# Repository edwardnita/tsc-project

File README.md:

# OpenBook - eBook Reader

**Autor:** Nita Eduard-Eugen
**Data:** 06 Aprilie 2025, updated pe 14 Aprilie 2025

## Bill of Materials (BOM)

| Component                | Link                                                                                                                      | Datasheet                                                                                                              |
|:-------------------------|:--------------------------------------------------------------------------------------------------------------------------|:-----------------------------------------------------------------------------------------------------------------------|
| BME680                   | [Link](https://www.snapeda.com/parts/BME680/Bosch/view-part/?welcome=home)                                                | [Datasheet](https://www.bosch-sensortec.com/media/boschsensortec/downloads/datasheets/bst-bme680-ds001.pdf)            |
| BUTTON                   | [Link](https://industry.panasonic.com/global/en/products/control/switch/light-touch/number/evqpuj02k)                     | [Datasheet](https://www.lcsc.com/datasheet/lcsc_datasheet_2201121800_PANASONIC-EVQPUJ02K_C2936858.pdf)                 |
| R0402                    | [Link](https://componentsearchengine.com/part-view/R0402%201%25%20100%20K%20(RC0402FR-07100KL)/YAGEO)                     | [Datasheet](https://www.resistor.com/assets/pdf/0402tstd.pdf)                                                          |
| CPH3225A                 | [Link](https://www.snapeda.com/parts/CPH3225A/Seiko+Instruments/view-part/?ref=eda)                                       | [Datasheet](https://octopart.com/datasheet/cph3225a-seiko-25340571)                                                    |
| EVQPUJ02K                | [Link](https://industry.panasonic.com/global/en/products/control/switch/light-touch/number/evqpuj02k)                     | [Datasheet](https://www.lcsc.com/datasheet/lcsc_datasheet_2201121800_PANASONIC-EVQPUJ02K_C2936858.pdf)                 |
| KP-1608SURCK             | [Link](https://www.snapeda.com/parts/KP-1608SURCK/Kingbright/view-part/?ref=search&t=LED%200603)                          | [Datasheet](https://media.elv.com/file/107153_led_surck1608_data.pdf)                                                  |
| USBLC6-2SC6Y             | [Link](https://www.snapeda.com/parts/USBLC6-2SC6Y/STMicroelectronics/view-part/?ref=eda)                                  | [Datasheet](https://www.digikey.com/en/htmldatasheets/production/1375342/0/0/1/usblc6-2sc6y)                           |
| SD0805S020S1R0           | [Link](https://ro.mouser.com/ProductDetail/KYOCERA-AVX/SD0805S020S1R0?qs=jCA%252BPfw4LHbpkAoSnwrdjw%3D%3D)                | [Datasheet](https://www.alldatasheet.com/view.jsp?Searchword=SD0805S&sField=2)                                         |
| PGB1010603MR             | [Link](https://www.snapeda.com/parts/PGB1010603MR/Littelfuse/view-part/?ref=eda)                                          | [Datasheet](https://www.alldatasheet.com/view.jsp?Searchword=Pgb1010603mr)                                             |
| BD5229G-TR               | [Link](https://componentsearchengine.com/part-view/BD5229G-TR/ROHM%20Semiconductor)                                       | [Datasheet](https://www.lcsc.com/datasheet/lcsc_datasheet_2201131330_ROHM-Semicon-BD5229G-TR_C962636.pdf)              |
| XC6220A331MR-G           | [Link](https://componentsearchengine.com/part-view/XC6220A331MR-G/Torex)                                                  | [Datasheet](https://www.alldatasheet.com/view.jsp?Searchword=Xc6220)                                                   |
| USB4110-GF-A             | [Link](https://componentsearchengine.com/part-view/USB4110-GF-A/GCT%20(GLOBAL%20CONNECTOR%20TECHNOLOGY))                  | [Datasheet](https://gct.co/files/drawings/usb4110.pdf)                                                                 |
| Adafruit LEDCHIP-LED0603 | [Link](https://eu.mouser.com/ProductDetail/Adafruit/4208?qs=PzGy0jfpSMtbScLbr0L5dw%3D%3D)                                 | [Datasheet](https://www.arrow.com/en/manufacturers/adafruit-industries/datasheets)                                     |
| Bobina                   | [Link](https://store.comet.srl.ro/Catalogue/Product/43497/)                                                               | [Datasheet](https://www.scribd.com/document/814581278/Datasheet-Bobina)                                                |
| PFMF                     | [Link](https://www.mouser.co.uk/ProductDetail/EPCOS-TDK/B72520T0350K062?qs=dEfas%2FXlABIszF52uu7vrg%3D%3D)                | [Datasheet](https://ro.mouser.com/c/ds/circuit-protection/thermistors/resettable-fuses-pptc/?m=Schurter&series=PFMF)   |
| DMG2305UX-7              | [Link](https://componentsearchengine.com/part-view/DMG2305UX-7/Diodes%20Incorporated)                                     | [Datasheet](https://www.mouser.com/datasheet/2/115/DMG2305UX-266242.pdf)                                               |
| Si1308EDL-T1-GE3         | [Link](https://componentsearchengine.com/part-view/SI1308EDL-T1-GE3/Vishay)                                               | [Datasheet](https://www.alldatasheet.com/view.jsp?Searchword=Si1308edl)                                                |
| MCP73831T-5ACI/OT        | [Link](https://www.mouser.co.uk/ProductDetail/Microchip-Technology/MCP73831T-5ACI-OT?qs=hH%252BOa0VZEiAcgAcEkuamXg%3D%3D) | [Datasheet](https://ww1.microchip.com/downloads/en/DeviceDoc/MCP73831-Family-Data-Sheet-DS20001984H.pdf)               |
| SMD Solder               | [Link](https://grabcad.com/library/solder-jumpers-1)                                                                      |                                                                                                                        |
| W25Q512JVEIQ             | [Link](https://www.snapeda.com/parts/ESP32-C6-WROOM-1-N8/Espressif+Systems/view-part/?ref=eda)                            | [Datasheet](https://www.mouser.com/datasheet/2/949/W25Q512JV_SPI_RevB_06252019_KMS-2487502.pdf)                        |
| ESP32-C6-WROOM-1-N8      | [Link](https://www.snapeda.com/parts/ESP32-C6-WROOM-1-N8/Espressif+Systems/view-part/?ref=eda)                            | [Datasheet](https://www.mouser.com/catalog/specsheets/Espressif_ESP32_C6_WROOM_1%20_Datasheet_V0.1_PRELIMINARY_en.pdf) |
| DS3231SN#                | [Link](https://www.snapeda.com/parts/DS3231SN%23/Analog+Devices/view-part/?ref=eda)                                       | [Datasheet](https://www.alldatasheet.com/view.jsp?Searchword=Ds3231sn%20datasheet)                                     |
| MAX17048G+T10            | [Link](https://www.snapeda.com/parts/MAX17048G+T10/Analog+Devices/view-part/?ref=eda)                                     | [Datasheet](https://www.alldatasheet.com/view.jsp?Searchword=Max17048)                                                 |

## Descriere Hardware

OpenBook este un e-reader open source care folosește ESP32-C6 ca unitate de control. Dispozitivul se concentrează pe eficiență energetică, conectivitate și afișaj de calitate tip e-ink.

### Microcontroller: ESP32-C6

- Procesor: RISC-V 32-bit @ 160 MHz
- Interfețe utilizate:
  - **SPI**: pentru e-paper
  - **I2C**: pentru BME688 și MAX17048
  - **USB-C**: pentru alimentare și transfer date
  - **GPIO**: pentru butoane și control încărcare

### Display: E-paper 7.5”

- Rezoluție: 800x480 px, alb-negru
- Interfață: SPI
- Refresh complet < 1s, parțial < 0.5s
- Folosit pentru afișare cărți, meniuri, informații senzori

### Senzor Mediu: BME688

- Măsoară: temperatură, umiditate, presiune, calitate aer (eCO2, TVOC)
- I2C, 400kHz
- Datele sunt afișate în interfața de utilizator și pot fi logate

### Power Management:

- **Baterie**: 2500mAh Li-Po 3.7V
- **MAX17048**: estimează nivelul de încărcare
- **MCP73831**: controlează încărcarea prin USB-C (1A max)
- **Consum**:
  - Active: ~120mA
  - Sleep: <50µA

### Butoane:

- 3 butoane fizice pentru meniu, navigare și selectare
- Interfață GPIO, debounce hardware/firmware

### USB-C:

- Alimentare și transfer fișiere (USB MSC)
- Protecție ESD

### PCB și Carcasă:

- PCB 2-layer cu layout optimizat termic și EMC
- ENIG finish
- Carcasă ABS/PC, 250g, ergonomică, rezistentă la praf și stropire (IP estimat: IP52)

## Pini ESP32-C6

| Componentă       | Pin ESP32-C6 | Motiv Alegere           |
| ---------------- | ------------ | ----------------------- |
| E-Paper SPI CLK  | GPIO10       | SPI hardware            |
| E-Paper SPI MOSI | GPIO11       | SPI hardware            |
| E-Paper CS       | GPIO9        | Chip Select dedicat     |
| BME688 I2C SDA   | GPIO4        | I2C standard            |
| BME688 I2C SCL   | GPIO5        | I2C standard            |
| MAX17048 SDA     | GPIO4        | I2C partajat cu BME688  |
| MAX17048 SCL     | GPIO5        | I2C partajat cu BME688  |
| Buton 1          | GPIO6        | Navigare                |
| Buton 2          | GPIO7        | Selectare               |
| Buton 3          | GPIO8        | Back/Menu               |
| USB D+           | GPIO18       | USB funcționalitate MSC |
| USB D-           | GPIO19       | USB funcționalitate MSC |

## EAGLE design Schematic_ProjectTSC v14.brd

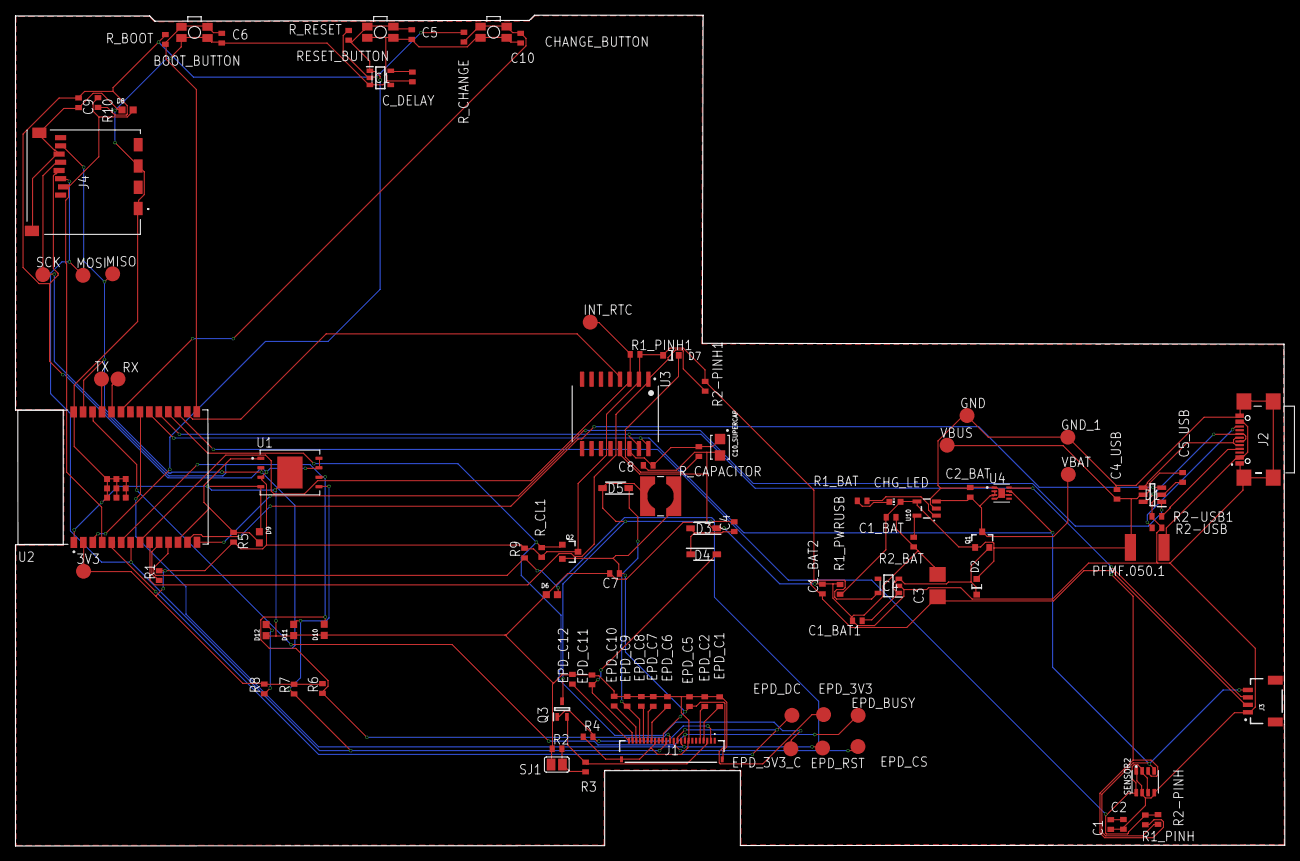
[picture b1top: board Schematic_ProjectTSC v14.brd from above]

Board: 2 copper layers, 170.2 x 111.4 mm, 103 parts (0 on the bottom side), 56 nets.

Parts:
3V3: TPTP20R; TP20R
BOOT_BUTTON: BUTTON_CUSYOMV1; MYBUTTON
C1: 100uF; EAGLE-LTSPICE_C0402
C1_BAT, C2_BAT: 4.7uF; ESP32_WROVER_EAGLE-LTSPICE_C0402
C1_BAT1, C1_BAT2, C5_USB: 4.7uF; EAGLE-LTSPICE_C0402
C2, C4_USB, C8, C9: 100nF; EAGLE-LTSPICE_C0402
C3: 100uF TANT; RCL_CT3528
C4: 4.7uF/25V; ESP32_WROVER_EAGLE-LTSPICE_C0402
C5: 1uF; ESP32_WROVER_EAGLE-LTSPICE_C0402
C6, C10: 100nF; ESP32_WROVER_EAGLE-LTSPICE_C0402
C7: 10uF; ESP32_WROVER_EAGLE-LTSPICE_C0402
C10_SUPERCAP: CPH3225A; CAPCP3225X100N
CHANGE_BUTTON: BUTTON_CUSYOMV1; MYBUTTON
CHG_LED: ADAFRUIT_CHIP-LED0603
C_DELAY: 100nF; ESP32_WROVER_EAGLE-LTSPICE_C0402
D1: USBLC6-2SC6Y; SOT95P280X145-6N
D2, D7: ESP32_WROVER_AVX---SD0805S020S1R0_AVX_SD0805S020S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; ESP32_WROVER_AVX---SD0805S020S1R0_AVX_SD0805S020S1R0_0
D3, D4, D5: MBR0530; SOD3716X135N
D6, D8, D9, D10, D11, D12: PGB1010603MR; DIOC1608X36N
EPD_3V3, EPD_3V3_C: TPTP20R; TP20R
EPD_BUSY: TPTP20R; TP20R
EPD_C1, EPD_C2, EPD_C6, EPD_C7, EPD_C8, EPD_C9, EPD_C10, EPD_C11, EPD_C12: 1uF/50V; ESP32_WROVER_EAGLE-LTSPICE_C0402
EPD_C5: 0.1uF/50V; ESP32_WROVER_EAGLE-LTSPICE_C0402
EPD_CS: TPTP20R; TP20R
EPD_DC: TPTP20R; TP20R
EPD_RST: TPTP20R; TP20R
GND: TPTP20R; TP20R
GND_1: TPTP20R; TP20R
IC1: BD5229G-TR; SOT95P280X125-5N
IC4: XC6220A331MR-G; SOT95P280X120-5N
INT_RTC: TPTP20R; TP20R
J1: FH34SRJ-24S-0.5SH_99_; FH34SRJ24S05SH99
J2: SAMACSYS_PARTS_USB4110-GF-A; SAMACSYS_PARTS_USB4110GFA
J3: QWIIC_RIGHT_ANGLE; JST04_1MM_RA
J4: 112A-TAAR-R03_ATTEND; 112ATAARR03ATTEND
L1: 744043680IND_4828-WE-TPC_WRE; IND_4828-WE-TPC_WRE
MISO: TPTP20R; TP20R
MOSI: TPTP20R; TP20R
PFMF.050.1: ESP32C6_VARISTORCN1812; ESP32C6_VARISTOR_CT/CN1812
Q1, Q2: 20V/4.2A/52mΩ/1.4W; ESP32_WROVER_SPARKFUN-DISCRETESEMI_SOT23-3
Q3: SI1308EDL-T1-GE3; SOT65P210X110-3N
R1, R1_PINH, R1_PINH1, R2-PINH, R2-PINH1, R4, R5, R6, R7, R8, R9, R10: 10K; ESP32_WROVER_EAGLE-LTSPICE_R0402
R1_BAT: 200; ESP32_WROVER_EAGLE-LTSPICE_R0402
R1_PWRUSB: 100k; ESP32_WROVER_EAGLE-LTSPICE_R0402
R2: 2.2; ESP32_WROVER_EAGLE-LTSPICE_R0402
R2-USB: 5K1; ESP32_WROVER_EAGLE-LTSPICE_R0402
R2-USB1: 5k1; ESP32_WROVER_EAGLE-LTSPICE_R0402
R2_BAT: 2K; ESP32_WROVER_EAGLE-LTSPICE_R0402
R3: 0.47; ESP32_WROVER_EAGLE-LTSPICE_R0402
RESET_BUTTON: BUTTON_CUSYOMV1; MYBUTTON
RX: TPTP20R; TP20R
R_BOOT: 10K; ESP32_WROVER_EAGLE-LTSPICE_R0402
R_CAPACITOR: 15; ESP32_WROVER_EAGLE-LTSPICE_R0402
R_CHANGE: 10K; ESP32_WROVER_EAGLE-LTSPICE_R0402
R_CL1: 10K; ESP32_WROVER_EAGLE-LTSPICE_R0402
R_RESET: 10K; ESP32_WROVER_EAGLE-LTSPICE_R0402
SCK: TPTP20R; TP20R
SENSOR2: ESP32_WROVER_BME680_BME680; ESP32_WROVER_BME680_PSON80P300X300X100-8N
SJ1: SJ
TX: TPTP20R; TP20R
U1: W25Q512JVEIQ; SON127P600X800X80-9N
U2: ESP32-C6-WROOM-1-N8; XCVR_ESP32-C6-WROOM-1-N8
U3: DS3231SN#; SOIC127P1032X265-16N
U4: MAX17048G+T10; SON50P200X200X80-9N
U10: ESP32_WROVER_SPARKFUN-IC-POWER_MCP73831; ESP32_WROVER_SPARKFUN-IC-POWER_SOT23-5
VBAT: TPTP20R; TP20R
VBUS: TPTP20R; TP20R

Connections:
3V3: 3V3.TP, C1_BAT2.1, C3.+, C9.1, D7.2, IC1.2, IC4.5, J3.2, J4.P4, Q2.3, R1.2, R1_PINH1.2, R2-PINH1.2, R5.2, R6.2, R7.2, R8.2, R9.2, R10.2, R_BOOT.2, R_CHANGE.2, R_CL1.2, R_RESET.2, U1.3, U1.7, U1.8, U2.2, U3.2
32KHZ: R2-PINH1.1, U2.9, U3.1
DN: D1.4, J2.A7, J2.B7
DP: D1.6, J2.A6, J2.B6
EPD_3V3: C7.1, EPD_3V3.TP, EPD_C5.1, J1.15, J1.16, L1.2, Q2.2
EPD_3V3_C: EPD_3V3_C.TP, Q2.1, R_CL1.1, U2.18
EPD_BUSY: EPD_BUSY.TP, J1.9, U2.26
EPD_CS: D6.2, EPD_CS.TP, J1.12, R9.1, U2.11
EPD_DC: EPD_DC.TP, J1.11, U2.5
EPD_RST: EPD_RST.TP, J1.10, U2.21
FLASH_CS: D9.2, R5.1, U1.1, U2.12
GDR: J1.2, Q3.1, R4.2
GND: BOOT_BUTTON.1, BOOT_BUTTON.2, C1.2, C1_BAT.2, C1_BAT1.2, C1_BAT2.2, C2.2, C2_BAT.2, C3.-, C4_USB.2, C5.2, C5_USB.2, C6.2, C7.2, C8.2, C9.2, C10.2, C10_SUPERCAP.2, CHANGE_BUTTON.1, CHANGE_BUTTON.2, C_DELAY.2, D1.2, D3.1, D6.1, D8.1, D9.1, D10.1, D11.1, D12.1, EPD_C1.2, EPD_C2.2, EPD_C5.2, EPD_C6.2, EPD_C7.2, EPD_C8.2, EPD_C9.2, EPD_C10.2, EPD_C11.2, EPD_C12.2, GND.TP, GND_1.TP, IC1.3, IC4.2, J1.8, J1.17, J1.MP1, J1.MP2, J2.A1, J2.A12, J2.B1, J2.B12, J2.MP1, J2.MP2, J2.MP3, J2.MP4, J3.1, J4.G1, J4.G2, J4.G3, J4.G4, J4.P6, R1_PWRUSB.1, R2.1, R2-USB.2, R2-USB1.1, R2_BAT.1, R4.1, RESET_BUTTON.1, RESET_BUTTON.2, SENSOR2.1, SENSOR2.5, SENSOR2.7, SJ1.1, U1.4, U1.9, U2.1, U2.28, U2.29_1, U2.29_2, U2.29_3, U2.29_4, U2.29_5, U2.29_6, U2.29_7, U2.29_8, U2.29_9, U3.13, U4.1, U4.4, U4.6, U4.9, U10.2
GPIO8: R1.1, U2.10
I2C_PW: R1_PINH.2, R2-PINH.2, SENSOR2.2, SENSOR2.6, SENSOR2.8, U2.17
INT_RTC: INT_RTC.TP, R1_PINH1.1, U2.8, U3.3
IO/BOOT: BOOT_BUTTON.3, BOOT_BUTTON.4, C6.1, R_BOOT.1, U2.15
IO/CHANGE: C10.1, CHANGE_BUTTON.3, CHANGE_BUTTON.4, R_CHANGE.1, U2.23
MISO: D12.2, J4.P7, MISO.TP, R8.1, U1.2, U2.27
MOSI: D11.2, J1.14, J4.P3, MOSI.TP, R7.1, U1.5, U2.7
unnamed: C1_BAT1.1, D2.1, IC4.1, IC4.3, Q1.2
unnamed: J2.B5, R2-USB.1
unnamed: R2_BAT.2, U10.5
unnamed: J2.A5, R2-USB1.2
unnamed: C1.1, C2.1
unnamed: C4.1, D3.2, D4.1
unnamed: C_DELAY.1, IC1.5
unnamed: CHG_LED.C, R1_BAT.1
unnamed: R1_BAT.2, U10.1
unnamed: EPD_C2.1, J1.5
unnamed: EPD_C1.1, J1.4
unnamed: EPD_C12.1, J1.24
unnamed: D7.1, R_CAPACITOR.1
unnamed: EPD_C10.1, J1.22
unnamed: EPD_C8.1, J1.20
unnamed: EPD_C7.1, J1.19
unnamed: EPD_C6.1, J1.18
PREVGH: D5.1, EPD_C9.1, J1.21
PREVGL: D4.2, EPD_C11.1, J1.23
RESE: J1.3, Q3.2, R3.2
RESE': R2.2, R3.1, SJ1.2
RESET: C5.1, IC1.1, RESET_BUTTON.3, RESET_BUTTON.4, R_RESET.1, U2.3
RTC_RST: U2.16, U3.4
RX: RX.TP, U2.24
SCK: D10.2, J1.13, J4.P5, R6.1, SCK.TP, U1.6, U2.6
SCL: J3.4, R2-PINH.1, SENSOR2.4, U2.20, U3.16, U4.7
SDA: J3.3, R1_PINH.1, SENSOR2.3, U2.19, U3.15, U4.8
SRC: C4.2, D5.2, L1.1, Q3.3
SS_SD: D8.2, J4.P2, R10.1, U2.4
TX: TX.TP, U2.25
USB_D+: D1.1, U2.14
USB_D-: D1.3, U2.13
VBAT: C2_BAT.1, Q1.3, U4.2, U4.3, U10.3, VBAT.TP
VBUS: C1_BAT.1, C4_USB.1, C5_USB.1, CHG_LED.A, D1.5, D2.2, PFMF.050.1.2, Q1.1, R1_PWRUSB.2, U10.4, VBUS.TP
VRTC: C8.1, C10_SUPERCAP.1, R_CAPACITOR.2, U3.14
VUSB: J2.A4, J2.A9, J2.B4, J2.B9, PFMF.050.1.1

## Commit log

2025-04-01 Added schematics file
2025-04-05 Added .brd file
2025-04-05 Added v0 of .stp
2025-04-06 Structured the files and readme
2025-04-14 Fixed issues

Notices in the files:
parts and their libraries:
COPYRIGHT: Copyright (C) 2024 Ultra Librarian. All rights reserved.
